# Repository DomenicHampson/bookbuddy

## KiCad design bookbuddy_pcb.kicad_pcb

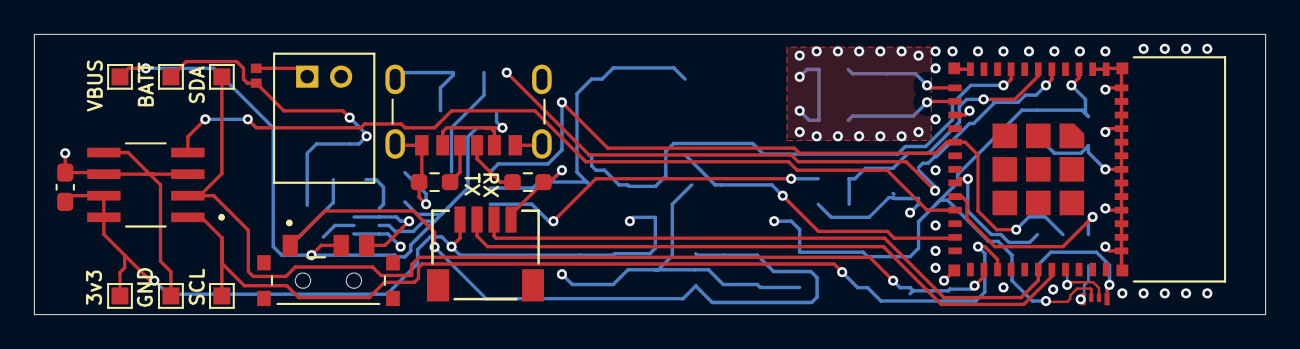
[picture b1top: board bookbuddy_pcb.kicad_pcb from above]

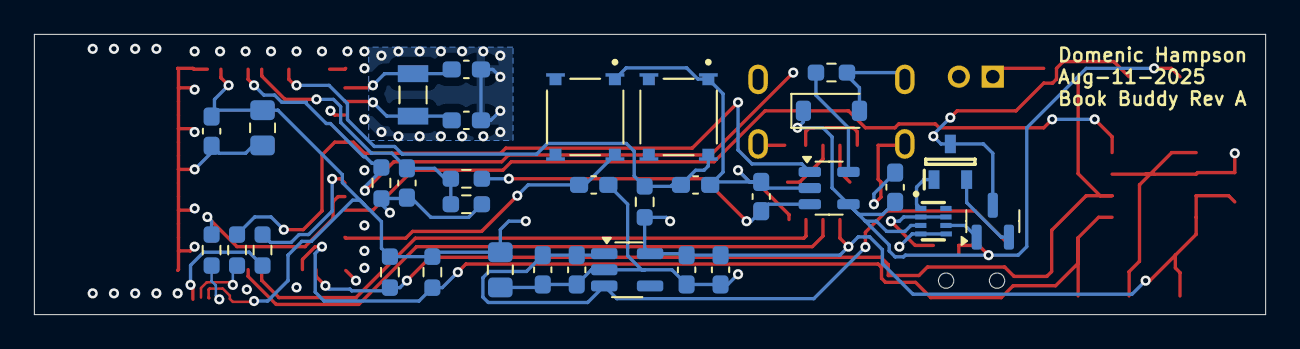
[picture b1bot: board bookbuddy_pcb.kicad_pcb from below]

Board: 4 copper layers, 72.5 x 16.5 mm, 50 parts (33 on the bottom side), 28 nets.

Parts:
3v3: +3v3; TestPoint_Pad_1.0x1.0mm
BATT: BATT; TestPoint_Pad_1.0x1.0mm
C1, C2: 8pF; C_0603_1608Metric_Pad1.08x0.95mm_HandSolder
C3, C5, C7, C8, C13: 0.1uF; C_0603_1608Metric_Pad1.08x0.95mm_HandSolder
C4: DNP; C_0805_2012Metric_Pad1.18x1.45mm_HandSolder
C6: 10uF; C_0805_2012Metric_Pad1.18x1.45mm_HandSolder
C9, C11: 1uF; C_0603_1608Metric_Pad1.08x0.95mm_HandSolder
C10, C12, C14, C15: 4.7uF; C_0603_1608Metric_Pad1.08x0.95mm_HandSolder
D2: SMF5.0A; D_SOD-123
F1: Fuse_Small; FUSC0402X49N
GND: GND; TestPoint_Pad_1.0x1.0mm
IC1: APX810S-31SA-7; SOT96P240X100-3N
IC2: LM66200DRLR; SOT8
J1: SM04B-SRSS-TB; CONN_SM04B-SRSS-TB_JST
J2: 10164359-00011LF; AMPHENOL_10164359-00011LF
J3: Battery Connector; JST_S2B-PH-K-S_LF__SN_
LED1: IN-S63TBS5R5G5B; IN-S63TBS5R5G5B_INO
Q1: DMG2305UX-13; SOT-23
R1, R2, R3, R4, R10: 10k; R_0603_1608Metric_Pad0.98x0.95mm_HandSolder
R5: 240; R_0603_1608Metric_Pad0.98x0.95mm_HandSolder
R6, R7: 39; R_0603_1608Metric_Pad0.98x0.95mm_HandSolder
R8, R9: 5.1k; R_0603_1608Metric_Pad0.98x0.95mm_HandSolder
R11: 100K 0.1%; R_0603_1608Metric_Pad0.98x0.95mm_HandSolder
R12: 249k 0.1%; R_0603_1608Metric_Pad0.98x0.95mm_HandSolder
SCL: SCL; TestPoint_Pad_1.0x1.0mm
SDA: SDA; TestPoint_Pad_1.0x1.0mm
SW1, SW2: SW_Push; SW_TL3315NF250Q
SW3: SLW-66527511-SMT-TR; SW_SLW-66527511-SMT-TR
U1: ESP32-C3-MINI-1; XCVR_ESP32-C3-MINI-1-N4
U2: MLX90395KDC-BBA-101-RE; SOIC127P600X172-8N
U3: MIC5504-3.3YM5-TR; SOT-23-5_HandSoldering
U4: MCP73832; SOT-23-5
VBUS: VBUS; TestPoint_Pad_1.0x1.0mm
Y1: 32.768kHz; XTAL_FC-135R_32.7680KA-AG0

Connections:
+3.3V: 3v3.1, C4.1, C5.1, C6.1, C8.1, C11.1, C12.1, J1.1, LED1.2, R1.2, R3.1, R4.1, U1.3 (3V3), U2.7 (VDD), U2.8 (MS/CS), U3.5 (VOUT)
+BATT: BATT.1, C15.1, F1.2, IC1.3 (VCC), Q1.3 (S), R11.2, U4.3 (VBAT)
/charging/BATT_PROT: IC2.6 (VIN2), Q1.1 (D)
/charging/BATT_V: C13.1, R11.1, R12.1, U1.6 (GPIO3/ADC1_CH3)
/charging/CHG_STAT: R6.1, U1.16 (GPIO10), U4.1 (STAT)
/hall_effect/SCL: R3.2, SCL.1, U1.27 (GPIO19/USB_D+), U2.1 (SCL/SCLK)
/hall_effect/SDA: R4.2, SDA.1, U1.26 (GPIO18/USB_D-), U2.2 (SDA/MOSI)
/hall_effect/TRIG: U1.21 (GPIO7), U2.4 (INT/TRG)
/mcu/B_LED: R7.1, U1.20 (GPIO6)
/mcu/G_LED: R5.1, U1.19 (GPIO5/ADC2_CH0)
/mcu/RX: J1.3, U1.30 (GPIO20/U0RXD)
/mcu/TX: J1.2, U1.31 (GPIO21/U0TXD)
GND: C1.1, C2.1, C3.1, C4.2, C5.2, C6.2, C7.1, C8.2, C9.2, C10.2, C11.2, C12.2, C13.2, C14.2, C15.2, D2.2 (A), GND.1, IC1.1 (GND), IC2.1 (GND@1), IC2.4 (ON), IC2.5 (GND@2), J1.4, J2.A12 (GND_A), J2.B12 (GND_B), J2.SH1 (SHIELD), J2.SH2 (SHIELD), J2.SH3 (SHIELD), J2.SH4 (SHIELD), J3.2, R2.2, R8.2, R9.1, R10.1, R12.2, SW1.1, SW2.1, U1.1 (GND), U1.2 (GND), U1.11 (GND), U1.14 (GND), U1.36 (GND), U1.37 (GND), U1.38 (GND), U1.39 (GND), U1.40 (GND), U1.41 (GND), U1.42 (GND), U1.43 (GND), U1.44 (GND), U1.45 (GND), U1.46 (GND), U1.47 (GND), U1.48 (GND), U1.50 (GND), U1.51 (GND), U1.52 (GND), U1.53 (GND), U2.3 (MISO), U2.5 (A0), U2.6 (VSS), U3.2 (GND), U4.2 (VSS)
unnamed: IC1.2 (RESET), Q1.2 (G)
unnamed: IC2.2 (VOUT@1), IC2.7 (VOUT@2), SW3.3 (A)
unnamed: J2.A5 (CC1), R8.1
unnamed: J2.B5 (CC2), R9.2
unnamed: F1.1, J3.1
unnamed: LED1.1, R7.2
unnamed: LED1.3, R6.2
unnamed: LED1.4, R5.2
unnamed: C9.1, C10.1, SW3.1 (B), U3.1 (VIN), U3.3 (EN)
unnamed: C3.2, R1.1, SW1.2, U1.8 (EN/CHIP_PU)
unnamed: C1.2, U1.12 (GPIO0/ADC1_CH0/XTAL_32K_P), Y1.2
unnamed: C2.2, U1.13 (GPIO1/ADC1_CH1/XTAL_32K_N), Y1.1
unnamed: C7.2, SW2.2, U1.23 (GPIO9)
unnamed: R10.2, U4.5 (PROG)
VBUS: C14.1, D2.1 (K), IC2.3 (VIN1), J2.A9 (VBUS_A), J2.B9 (VBUS_B), R2.1, SW3.2 (C), U1.5 (GPIO2/ADC1_CH2), U4.4 (VDD), VBUS.1

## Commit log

2025-07-17 Initial commit of PCB files
2025-07-17 Added footprint library
2025-07-17 symbols/footprints hooked up
2025-07-17 added test points
2025-07-22 Made changes up to diode logic
2025-07-23 made remaining changes to the schematic
2025-07-23 updated pcb layout quickly
2025-08-12 addressed Craig's comments
2025-08-13 Added fuse
2025-08-13 switched to 4 layer
2025-08-20 finished routing the pcb
